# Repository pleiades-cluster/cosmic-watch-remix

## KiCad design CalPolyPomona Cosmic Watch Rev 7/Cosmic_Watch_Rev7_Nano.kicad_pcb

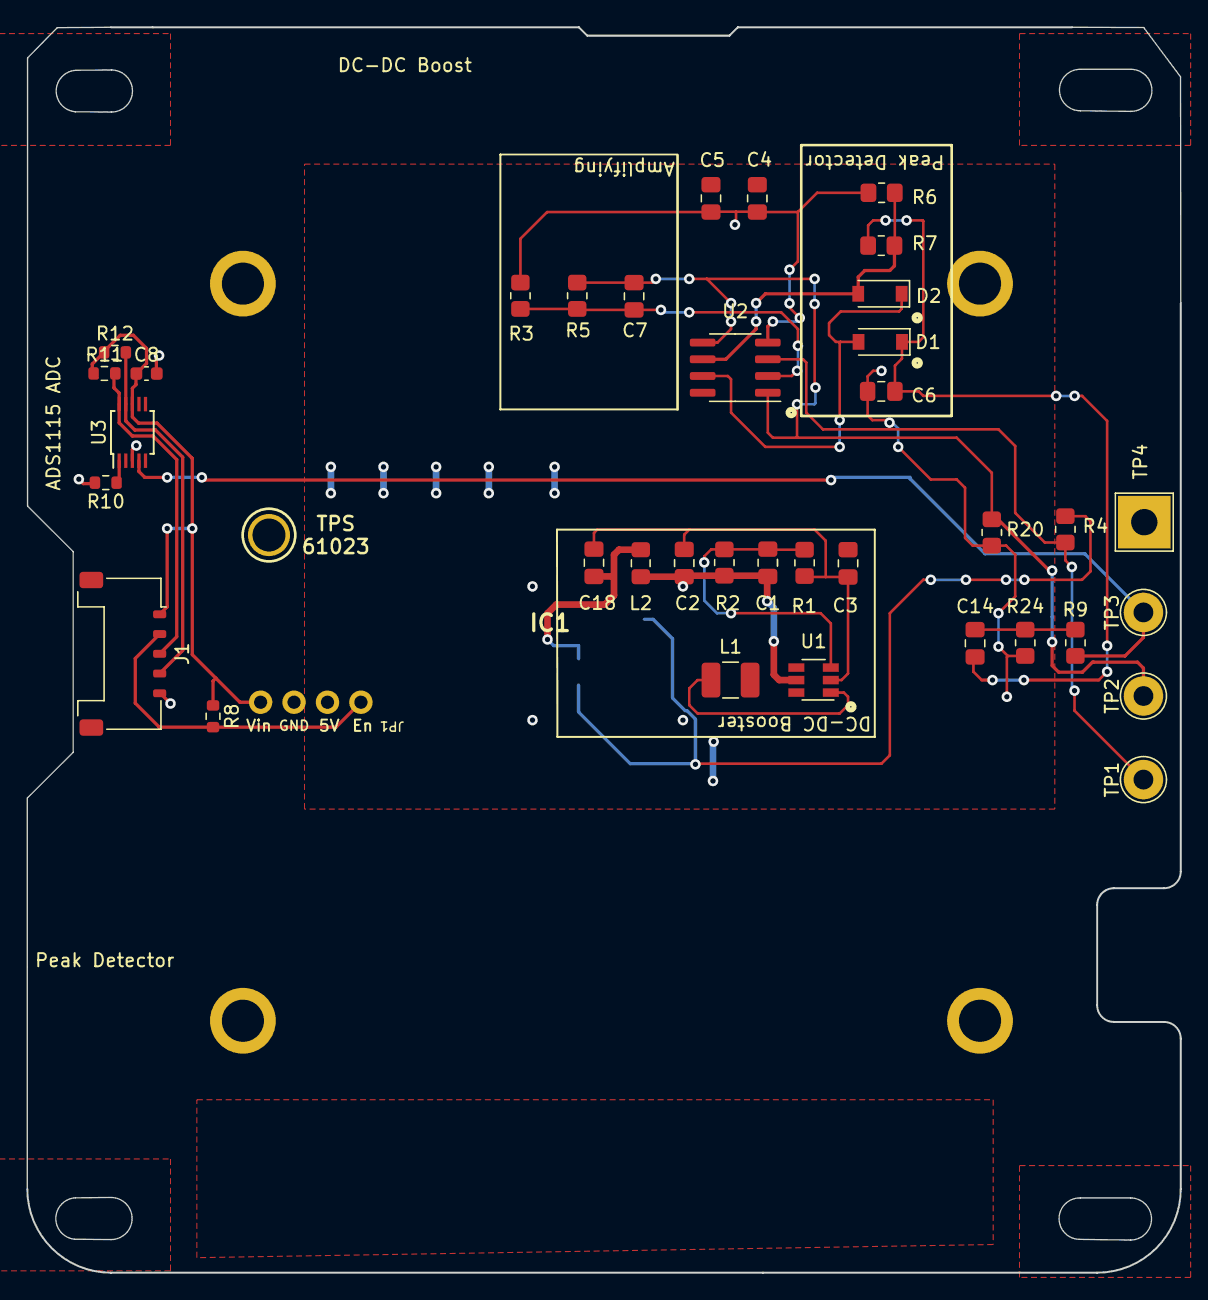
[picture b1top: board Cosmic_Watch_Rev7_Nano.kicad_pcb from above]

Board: 2 copper layers, 87.6 x 94.6 mm, 38 parts (1 on the bottom side), 20 nets.

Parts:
C1: 22pF; C_0805_2012Metric_Pad1.18x1.45mm_HandSolder
C2: 0.47pF; C_0805_2012Metric_Pad1.18x1.45mm_HandSolder
C3, C18: 1uF; C_0805_2012Metric_Pad1.18x1.45mm_HandSolder
C4: 10uF; C_0805_2012Metric_Pad1.18x1.45mm_HandSolder
C5: 0.1uF; C_0805_2012Metric_Pad1.18x1.45mm_HandSolder
C6: 20nF; C_0805_2012Metric_Pad1.18x1.45mm_HandSolder
C7: 10pF; C_0805_2012Metric_Pad1.18x1.45mm_HandSolder
C8: 0.1; C_0603_1608Metric
C14: 0F; C_0805_2012Metric_Pad1.18x1.45mm_HandSolder
D1, D2: 40V 500mA; D_SOD-123
IC1: MICROFJ-60035-TSV-TR1; MICROFJ60035TSVTR1
J1: Conn_01x05_Female; Molex_Pico-Lock_504050-0591_1x05-1MP_P1.50mm_Horizontal
L1: 47uH; L_1210_3225Metric_Pad1.42x2.65mm_HandSolder
L2: 2.5k Ohms; L_0805_2012Metric_Pad1.15x1.40mm_HandSolder
R1, R5, R20: 10k; R_0805_2012Metric_Pad1.20x1.40mm_HandSolder
R2: 226k; R_0805_2012Metric_Pad1.20x1.40mm_HandSolder
R3: 249; R_0805_2012Metric_Pad1.20x1.40mm_HandSolder
R4: 1k; R_0805_2012Metric_Pad1.20x1.40mm_HandSolder
R6, R7: 100k; R_0805_2012Metric_Pad1.20x1.40mm_HandSolder
R8, R10, R11, R12: 10K; R_0603_1608Metric
R9: 0k; R_0805_2012Metric_Pad1.20x1.40mm_HandSolder
R24: 24.9k; R_0805_2012Metric_Pad1.20x1.40mm_HandSolder
TP1, TP2, TP3: Test_Point1; TestPoint_THTPad_D3.0mm_Drill1.5mm
TP4: GND; TestPoint_THTPad_4.0x4.0mm_Drill2.0mm
U1: LT3461ES6#TRPBF; TSOT-23-6
U2: LT1807IS8#PBF; SOIC-8_3.9x4.9mm_P1.27mm
U3: ADS1115IDGS; TSSOP-10_3x3mm_P0.5mm
U$9: MOUNTINGHOLE2.5; MOUNTINGHOLE_2.5_PLATED

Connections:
+5V: C3.1, C4.1, C5.1, L1.2, U1.4 (SHDN), U1.6 (Vin), U2.8 (V+)
GND: C2.2, C3.2, C4.2, C5.2, C6.2, C8.2, C18.2, IC1.A2 (NO_CONNECT_1), IC1.A3 (NO_CONNECT_2), IC1.A4 (NO_CONNECT_3), IC1.A5 (NO_CONNECT_4), IC1.A6 (NO_CONNECT_5), IC1.B1 (NO_CONNECT_6), IC1.B2 (NO_CONNECT_7), IC1.B3 (NO_CONNECT_8), IC1.B4 (NO_CONNECT_9), IC1.B5 (NO_CONNECT_10), IC1.B6 (NO_CONNECT_11), IC1.C2 (NO_CONNECT_12), IC1.C3 (NO_CONNECT_13), IC1.C4 (NO_CONNECT_14), IC1.C5 (NO_CONNECT_15), IC1.D2 (NO_CONNECT_16), IC1.D3 (NO_CONNECT_17), IC1.D4 (NO_CONNECT_18), IC1.D5 (NO_CONNECT_19), IC1.E1 (NO_CONNECT_20), IC1.E2 (NO_CONNECT_21), IC1.E3 (NO_CONNECT_22), IC1.E4 (NO_CONNECT_23), IC1.E5 (NO_CONNECT_24), IC1.E6 (NO_CONNECT_25), IC1.F1 (NO_CONNECT_26), IC1.F2 (NO_CONNECT_27), IC1.F3 (NO_CONNECT_28), IC1.F4 (NO_CONNECT_29), IC1.F5 (NO_CONNECT_30), J1.5, R1.2, R3.2, R6.2, R10.2, R20.2, R24.2, TP4.1, U1.2 (gnd), U2.4 (V-), U3.3 (GND)
unnamed: C1.1, C2.1, L2.1, R2.2, U1.5 (Vout)
unnamed: C1.2, R1.1, R2.1, U1.3 (FB)
unnamed: C7.1, R3.1, R5.1, U2.2 (-IN_A)
unnamed: C7.2, R5.2, R20.1, TP2.1 (TP1), U2.1 (OUT_A), U2.5 (+IN_B)
unnamed: C6.1, C14.1, D1.1 (K), R7.2
unnamed: C14.2, R9.1, R24.1
unnamed: C18.1, IC1.C6 (FAST_OUTPUT_1), IC1.D6 (FAST_OUTPUT_2), L2.2
unnamed: D1.2 (A), D2.1 (K), U2.7 (OUT_B)
unnamed: D2.2 (A), R6.1, R7.1, U2.6 (-IN_B)
unnamed: IC1.A1 (CATHODE_1), IC1.F6 (CATHODE_2), R4.1
unnamed: J1.2, R8.2
unnamed: J1.3, R11.2, U3.10 (SCL)
unnamed: J1.4, R12.2, U3.9 (SDA)
unnamed: L1.1, U1.1 (sw)
unnamed: R4.2, TP1.1 (TP1), U2.3 (+IN_A)
unnamed: R9.2, TP3.1 (TP1), U3.4 (AIN0)
unnamed: R10.1, U3.1 (ADDR)
VCC: C8.1, J1.1, R8.1, R11.1, R12.1

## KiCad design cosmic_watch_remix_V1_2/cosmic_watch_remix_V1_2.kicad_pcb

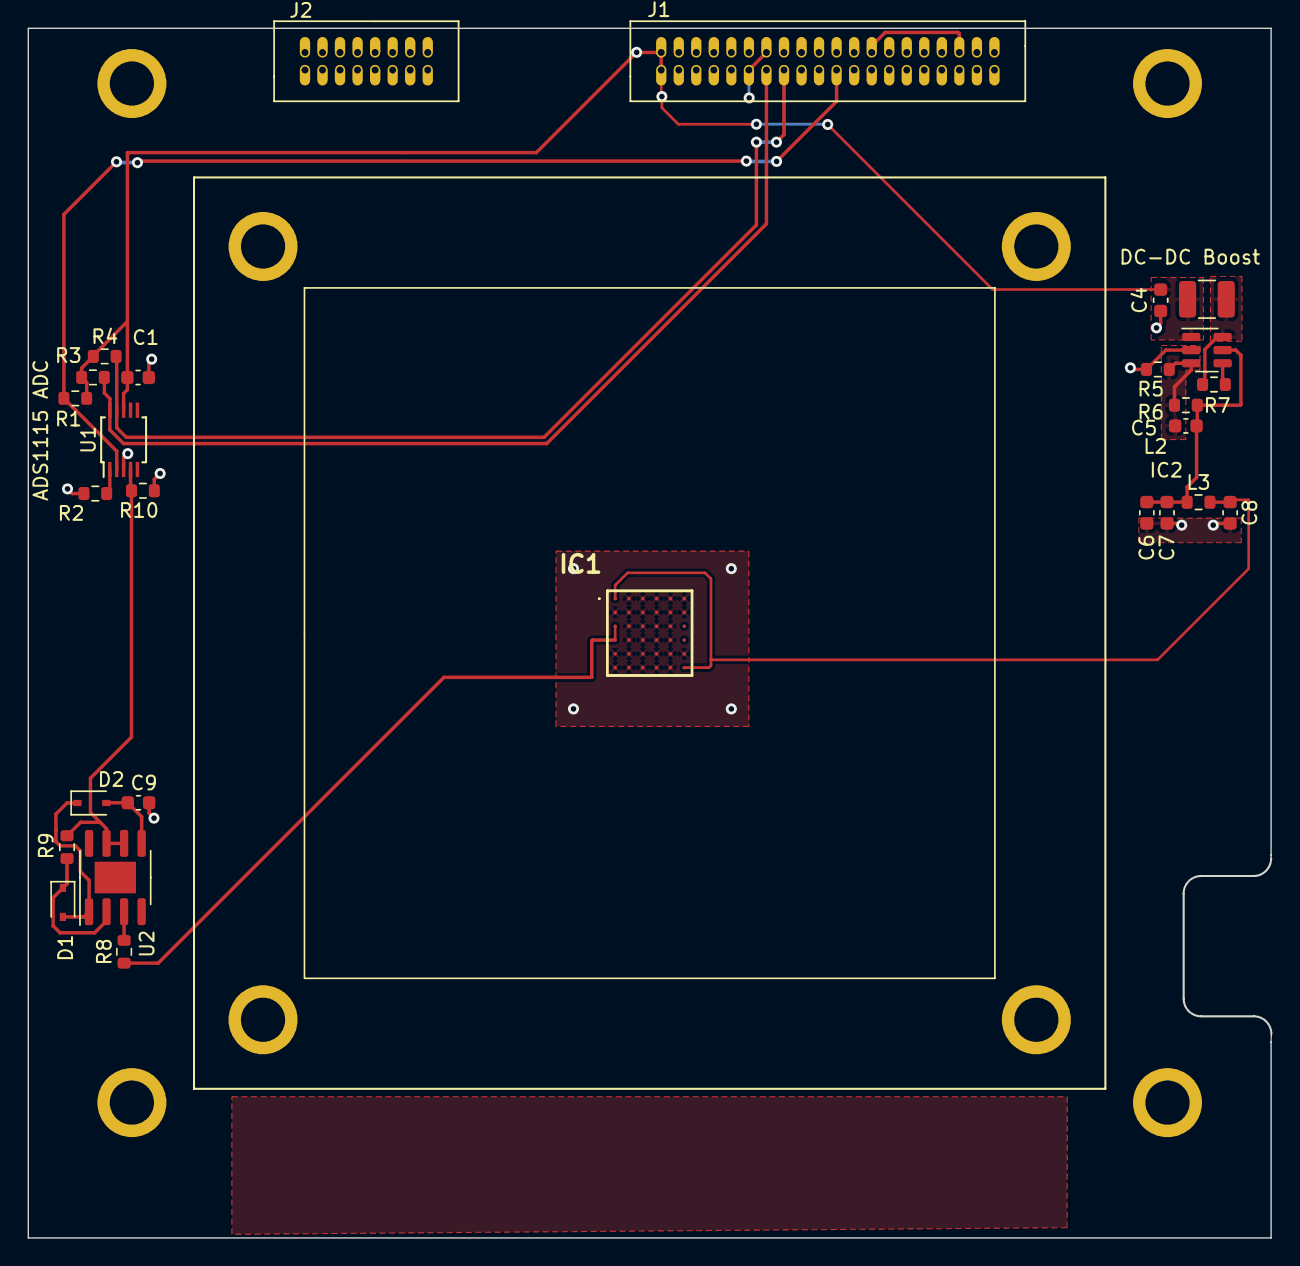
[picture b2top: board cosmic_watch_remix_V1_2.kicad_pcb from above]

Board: 2 copper layers, 90.0 x 87.6 mm, 27 parts (0 on the bottom side), 16 nets.

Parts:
C1: 0.1; C_0603_1608Metric
C4, C6, C8: 1uF; C_0603_1608Metric
C5: 50pF; C_0603_1608Metric
C7: 0.47pF; C_0603_1608Metric
C9: 20nF; C_0603_1608Metric
D1, D2: DIODE; D_SOD-323
IC1: MICROFJ-60035-TSV-TR1; MICROFJ60035TSVTR1
IC2: LT3461AES6#TRMPBF; TSOT-23-6
J1: Conn_02x20_Odd_Even; 40_Pin_For_Proves
J2: Conn_02x08_Odd_Even; 16_Pin_For_Proves
L2: 18uH; L_1210_3225Metric
L3: 2.5k Ferrite; R_0603_1608Metric
R1, R2, R3, R4, R5, R7, R8, R9: 10K; R_0603_1608Metric
R6: 280K; R_0603_1608Metric
R10: 100k; R_0603_1608Metric
U1: ADS1115IDGS; TSSOP-10_3x3mm_P0.5mm
U2: LM358; SOIC-8-1EP_3.9x4.9mm_P1.27mm_EP2.29x3mm

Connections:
/VIN: IC2.6 (VIN), L2.2, R7.1
/VOUT: C5.1, C6.1, C7.1, IC2.5 (VOUT), L3.1, R6.2
GND: C1.2, C4.2, C6.2, C7.2, C8.2, C9.2, IC1.A2 (NO_CONNECT_1), IC1.A3 (NO_CONNECT_2), IC1.A4 (NO_CONNECT_3), IC1.A5 (NO_CONNECT_4), IC1.A6 (NO_CONNECT_5), IC1.B1 (NO_CONNECT_6), IC1.B2 (NO_CONNECT_7), IC1.B3 (NO_CONNECT_8), IC1.B4 (NO_CONNECT_9), IC1.B5 (NO_CONNECT_10), IC1.B6 (NO_CONNECT_11), IC1.C2 (NO_CONNECT_12), IC1.C3 (NO_CONNECT_13), IC1.C4 (NO_CONNECT_14), IC1.C5 (NO_CONNECT_15), IC1.D2 (NO_CONNECT_16), IC1.D3 (NO_CONNECT_17), IC1.D4 (NO_CONNECT_18), IC1.D5 (NO_CONNECT_19), IC1.E1 (NO_CONNECT_20), IC1.E2 (NO_CONNECT_21), IC1.E3 (NO_CONNECT_22), IC1.E4 (NO_CONNECT_23), IC1.E5 (NO_CONNECT_24), IC1.E6 (NO_CONNECT_25), IC1.F1 (NO_CONNECT_26), IC1.F2 (NO_CONNECT_27), IC1.F3 (NO_CONNECT_28), IC1.F4 (NO_CONNECT_29), IC1.F5 (NO_CONNECT_30), IC2.2 (GND), J1.11, J1.14, J1.17, J1.19, J1.26, J1.35, J1.36, J1.37, J1.39, R2.2, R5.2, R10.1, U1.3 (GND)
unnamed: C5.2, IC2.3 (FB), R5.1, R6.1
unnamed: C9.1, D2.2 (K), U2.5 (+)
unnamed: D1.1 (A), R9.1
unnamed: D1.2 (K), D2.1 (A)
unnamed: IC1.C1 (ANODE_1), IC1.D1 (ANODE_2), R8.1
unnamed: IC2.4 (~SHDN), R7.2
unnamed: J1.13, R3.2, U1.10 (SCL)
unnamed: J1.15, R4.2, U1.9 (SDA)
unnamed: J1.21, R1.2, U1.2 (ALERT/RDY)
unnamed: R2.1, U1.1 (ADDR)
unnamed: R9.2, R10.2, U1.4 (AIN0), U2.6 (-), U2.7
VBIAS: C8.1, IC1.A1 (CATHODE_1), IC1.F6 (CATHODE_2), L3.2
VCC: C1.1, C4.1, IC2.1 (SW), J1.01, J1.02, L2.1, R1.1, R3.1, R4.1, U1.8 (VDD)

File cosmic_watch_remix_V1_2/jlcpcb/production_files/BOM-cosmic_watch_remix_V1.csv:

Comment,Designator,Footprint,LCSC
2.5k Ferrite,L3,R_0603_1608Metric,C1002
0.1,C1,C_0603_1608Metric,C14663
1uF,"C4,C6,C8",C_0603_1608Metric,C15849
50pF,C5,C_0603_1608Metric,C1672
DIODE,"D1,D2",D_SOD-323,C191023
?,C9,C_0603_1608Metric,C21122
280K,R6,R_0603_1608Metric,C22961
18uH,L2,L_1210_3225Metric,C250186
?,R10,R_0603_1608Metric,C25803
10K,"R1,R2,R3,R4,R5,R7,R8,R9",R_0603_1608Metric,C25804
ADS1115IDGS,U1,TSSOP-10_3x3mm_P0.5mm,C37593
LT3461AES6#TRMPBF,IC2,TSOT-23-6,C481768
0.47pF,C7,C_0603_1608Metric,C519378
LM358,U2,SOIC-8-1EP_3.9x4.9mm_P1.27mm_EP2.29x3mm,C7950
Conn_01x05_Female,J1,Molex_Pico-Lock_504050-0591_1x05-1MP_P1.50mm_Horizontal,
MICROFJ-60035-TSV-TR1,IC1,MICROFJ60035TSVTR1,

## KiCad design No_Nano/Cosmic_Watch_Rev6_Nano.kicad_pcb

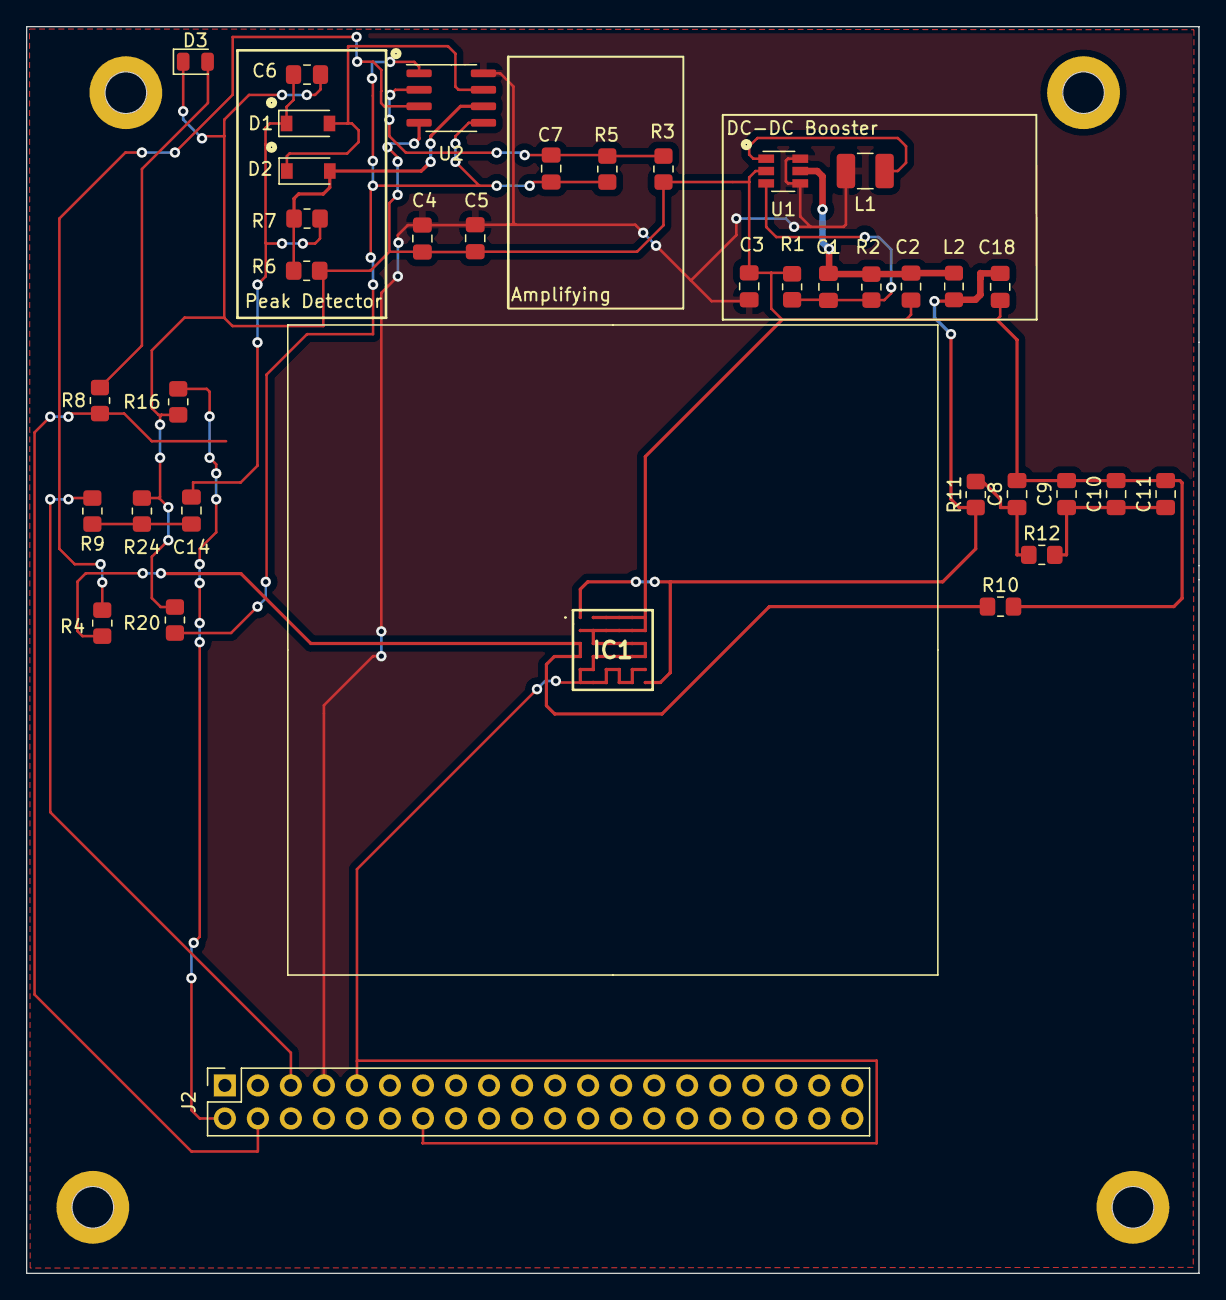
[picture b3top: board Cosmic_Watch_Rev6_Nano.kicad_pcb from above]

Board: 2 copper layers, 90.2 x 95.9 mm, 37 parts (0 on the bottom side), 20 nets.

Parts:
C1: 22pF; C_0805_2012Metric_Pad1.18x1.45mm_HandSolder
C2: 0.47pF; C_0805_2012Metric_Pad1.18x1.45mm_HandSolder
C3, C8, C9, C10, C11, C18: 1uF; C_0805_2012Metric_Pad1.18x1.45mm_HandSolder
C4: 10uF; C_0805_2012Metric_Pad1.18x1.45mm_HandSolder
C5: 0.1uF; C_0805_2012Metric_Pad1.18x1.45mm_HandSolder
C6: 20nF; C_0805_2012Metric_Pad1.18x1.45mm_HandSolder
C7: 10pF; C_0805_2012Metric_Pad1.18x1.45mm_HandSolder
C14: 0F; C_0805_2012Metric_Pad1.18x1.45mm_HandSolder
D1, D2: 40V 500mA; D_SOD-123
D3: LED; LED_0805_2012Metric
IC1: MICROFJ-60035-TSV-TR1; MICROFJ60035TSVTR1
J2: Conn_02x20_Odd_Even; PinSocket_2x20_P2.54mm_Vertical
L1: 47uH; L_1210_3225Metric_Pad1.42x2.65mm_HandSolder
L2: 2.5k Ohms; L_0805_2012Metric_Pad1.15x1.40mm_HandSolder
R1, R5, R16, R20: 10k; R_0805_2012Metric_Pad1.20x1.40mm_HandSolder
R2: 226k; R_0805_2012Metric_Pad1.20x1.40mm_HandSolder
R3: 249; R_0805_2012Metric_Pad1.20x1.40mm_HandSolder
R4, R8, R10, R11, R12: 1k; R_0805_2012Metric_Pad1.20x1.40mm_HandSolder
R6, R7: 100k; R_0805_2012Metric_Pad1.20x1.40mm_HandSolder
R9: 0k; R_0805_2012Metric_Pad1.20x1.40mm_HandSolder
R24: 24.9k; R_0805_2012Metric_Pad1.20x1.40mm_HandSolder
U1: LT3461ES6#TRPBF; TSOT-23-6
U2: LT1807IS8#PBF; SOIC-8_3.9x4.9mm_P1.27mm

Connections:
+5V: C3.1, C4.1, C5.1, J2.7, L1.2, U1.4 (SHDN), U1.6 (Vin), U2.8 (V+)
GND: C2.2, C3.2, C4.2, C5.2, C6.2, C8.2, C9.2, C10.2, C11.2, C18.2, D3.1 (K), IC1.A2 (NO_CONNECT_1), IC1.A3 (NO_CONNECT_2), IC1.A4 (NO_CONNECT_3), IC1.A5 (NO_CONNECT_4), IC1.A6 (NO_CONNECT_5), IC1.B1 (NO_CONNECT_6), IC1.B2 (NO_CONNECT_7), IC1.B3 (NO_CONNECT_8), IC1.B4 (NO_CONNECT_9), IC1.B5 (NO_CONNECT_10), IC1.B6 (NO_CONNECT_11), IC1.C2 (NO_CONNECT_12), IC1.C3 (NO_CONNECT_13), IC1.C4 (NO_CONNECT_14), IC1.C5 (NO_CONNECT_15), IC1.C6 (FAST_OUTPUT_1), IC1.D2 (NO_CONNECT_16), IC1.D3 (NO_CONNECT_17), IC1.D4 (NO_CONNECT_18), IC1.D5 (NO_CONNECT_19), IC1.D6 (FAST_OUTPUT_2), IC1.E1 (NO_CONNECT_20), IC1.E2 (NO_CONNECT_21), IC1.E3 (NO_CONNECT_22), IC1.E4 (NO_CONNECT_23), IC1.E5 (NO_CONNECT_24), IC1.E6 (NO_CONNECT_25), IC1.F1 (NO_CONNECT_26), IC1.F2 (NO_CONNECT_27), IC1.F3 (NO_CONNECT_28), IC1.F4 (NO_CONNECT_29), IC1.F5 (NO_CONNECT_30), J2.9, J2.14, R1.2, R3.2, R6.2, R10.2, R16.2, R20.2, R24.2, U1.2 (gnd), U2.4 (V-)
unnamed: C1.1, C2.1, L2.1, R2.2, U1.5 (Vout)
unnamed: C1.2, R1.1, R2.1, U1.3 (FB)
unnamed: C7.1, R3.1, R5.1, U2.2 (-IN_A)
unnamed: C7.2, R5.2, R20.1, U2.1 (OUT_A), U2.5 (+IN_B)
unnamed: C8.1, R11.2, R12.1
unnamed: C9.1, C10.1, C11.1, R12.2
unnamed: C6.1, C14.1, D1.1 (K), R7.2
unnamed: C14.2, R9.1, R24.1
unnamed: C18.1, IC1.A1 (CATHODE_1), IC1.F6 (CATHODE_2), L2.2, R11.1
unnamed: D1.2 (A), D2.1 (K), U2.7 (OUT_B)
unnamed: D2.2 (A), R6.1, R7.1, U2.6 (-IN_B)
unnamed: D3.2 (A), R8.1
unnamed: IC1.C1 (ANODE_1), IC1.D1 (ANODE_2), R4.1, R10.1
unnamed: L1.1, U1.1 (sw)
unnamed: R4.2, U2.3 (+IN_A)
unnamed: J2.4, R8.2
unnamed: J2.5, R9.2
unnamed: J2.2, R16.1

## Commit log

2022-12-31 Initial Empty KiCAD Project
2023-01-01 Board Progress
    Working on schematic
2023-01-07 Merged MQ No_Nano Revision
2023-01-07 Component Initial Layout Complete
2023-01-09 V1.0
    Finished Layout, Ready to Review!
2023-01-12 Completed Component Selection
    Note change to 28V output
2023-01-21 Updated Production Files
2023-01-28 Fixed Inductor Power Path
2023-03-15 Created Rev 7 of Original CPP Cosmic Watch Design
2023-03-24 As Ordered Mar 23
